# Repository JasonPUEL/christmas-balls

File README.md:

# Christmas Balls

Realization of Christmas ball in PCB, for the pleasure of young and old.
The principle is to build a colored printed circuit.
Programmable colored LEDs will be implemented in a design directly referring to the Christmas spirit.

## General idea

The Christmas balls will have to be autonomous to last the time of the end of year celebrations.
It must be on battery or on pilsner with a small, energy-efficient microcontroller.

A Christmas design should be simple and easily recognizable. It will integrate LEDs cost effectively.

## Shematic

## Board

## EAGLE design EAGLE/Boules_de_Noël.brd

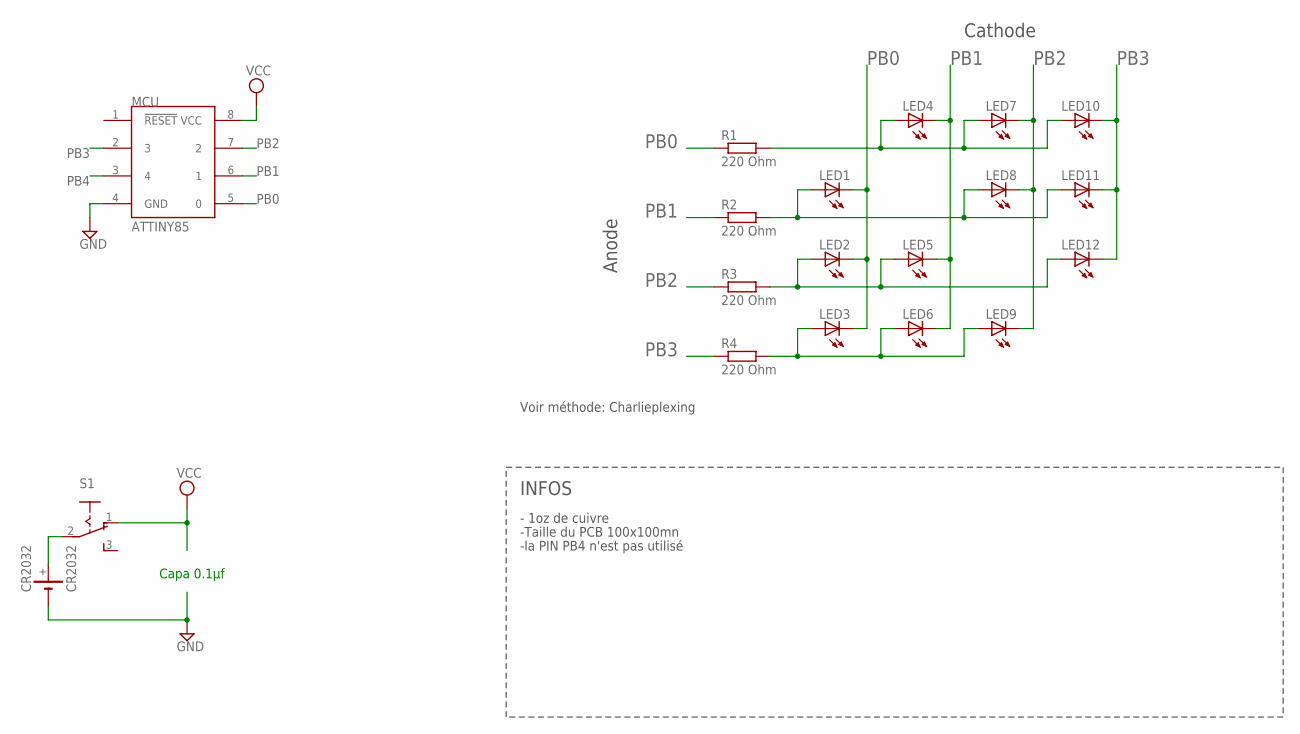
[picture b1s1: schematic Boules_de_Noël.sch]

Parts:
CR2032: CR2032; FRONTCR2032
LED1, LED2, LED3, LED4, LED5, LED6, LED7, LED8, LED9, LED10, LED11, LED12: LEDCHIP-LED0805; CHIP-LED0805
MCU: ATTINY85; 8P3
R1, R2, R3, R4: 220 Ohm; M0805
S1: 255SB

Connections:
GND: CR2032.-, MCU.4 (GND)
unnamed: CR2032.+, S1.2
PB0: LED1.C, LED2.C, LED3.C, MCU.5 (0), R1.1
PB1: LED4.C, LED5.C, LED6.C, MCU.6 (1), R2.1
PB2: LED7.C, LED8.C, LED9.C, MCU.7 (2), R3.1
PB3: LED10.C, LED11.C, LED12.C, MCU.2 (3), R4.1
PB4: MCU.3 (4)
R1: LED4.A, LED7.A, LED10.A, R1.2
R2: LED1.A, LED8.A, LED11.A, R2.2
R3: LED2.A, LED5.A, LED12.A, R3.2
R4: LED3.A, LED6.A, LED9.A, R4.2
VCC: MCU.8 (VCC), S1.1 (O)

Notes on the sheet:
INFOS
Anode
Cathode
- 1oz de cuivre
-Taille du PCB 100x100mn
-la PIN PB4 n'est pas utilisé
Voir méthode: Charlieplexing
Capa 0.1µf

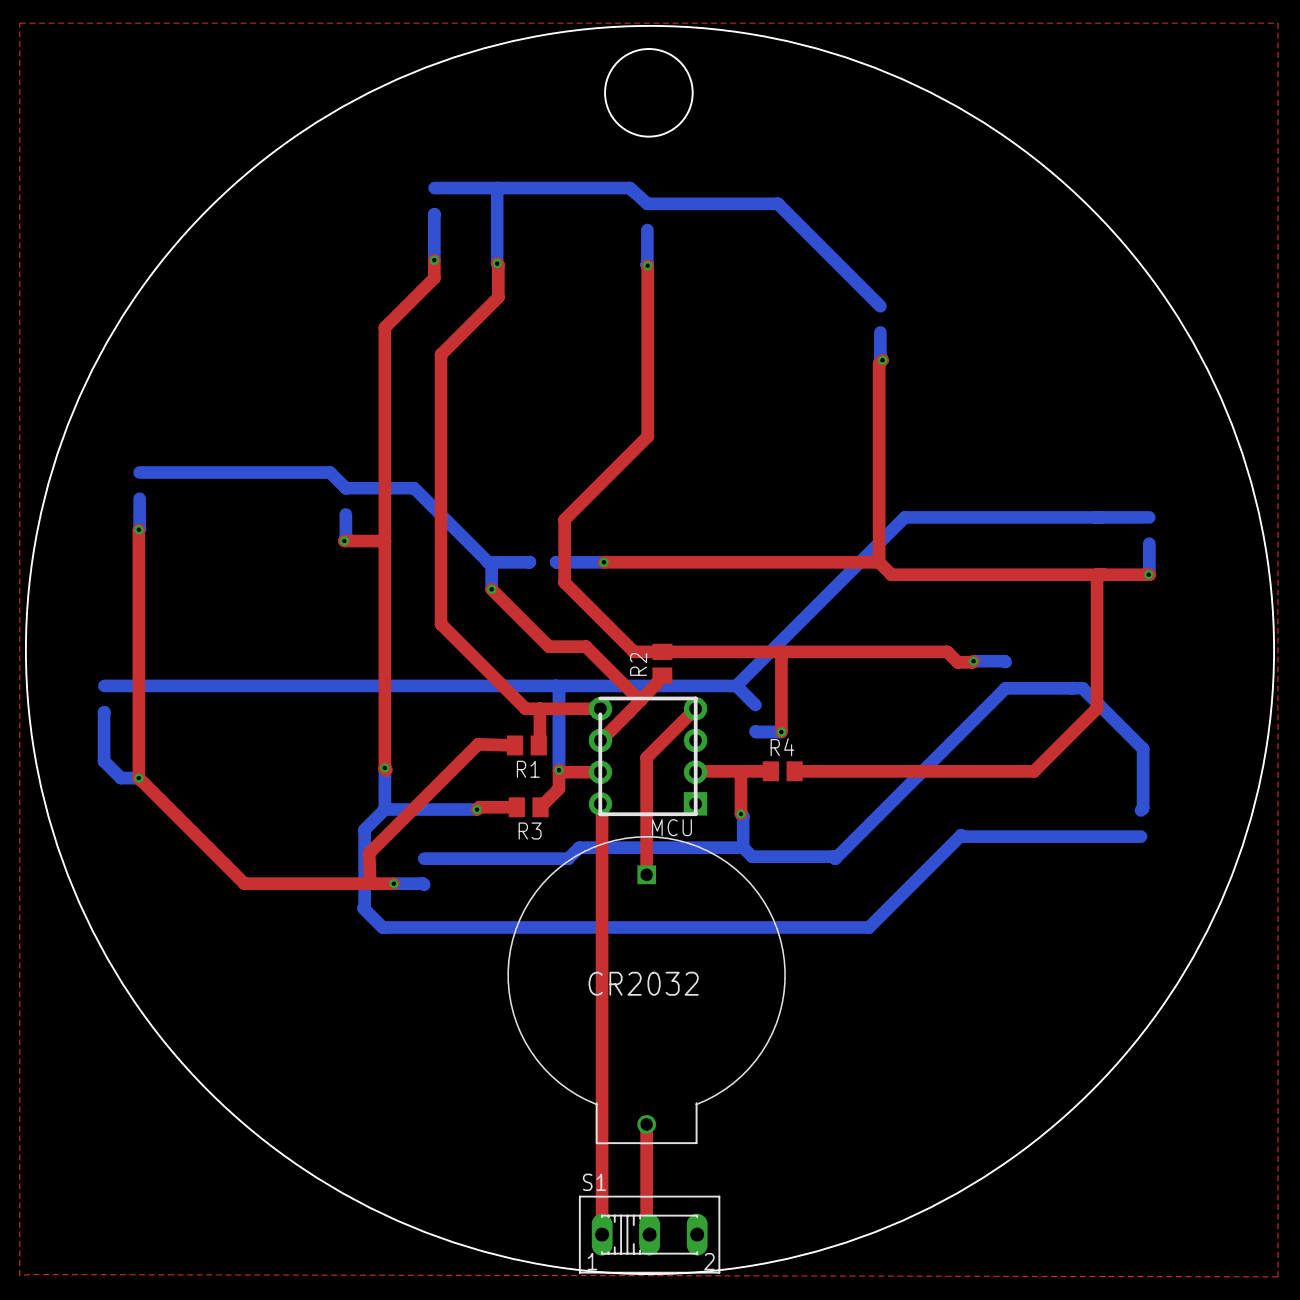
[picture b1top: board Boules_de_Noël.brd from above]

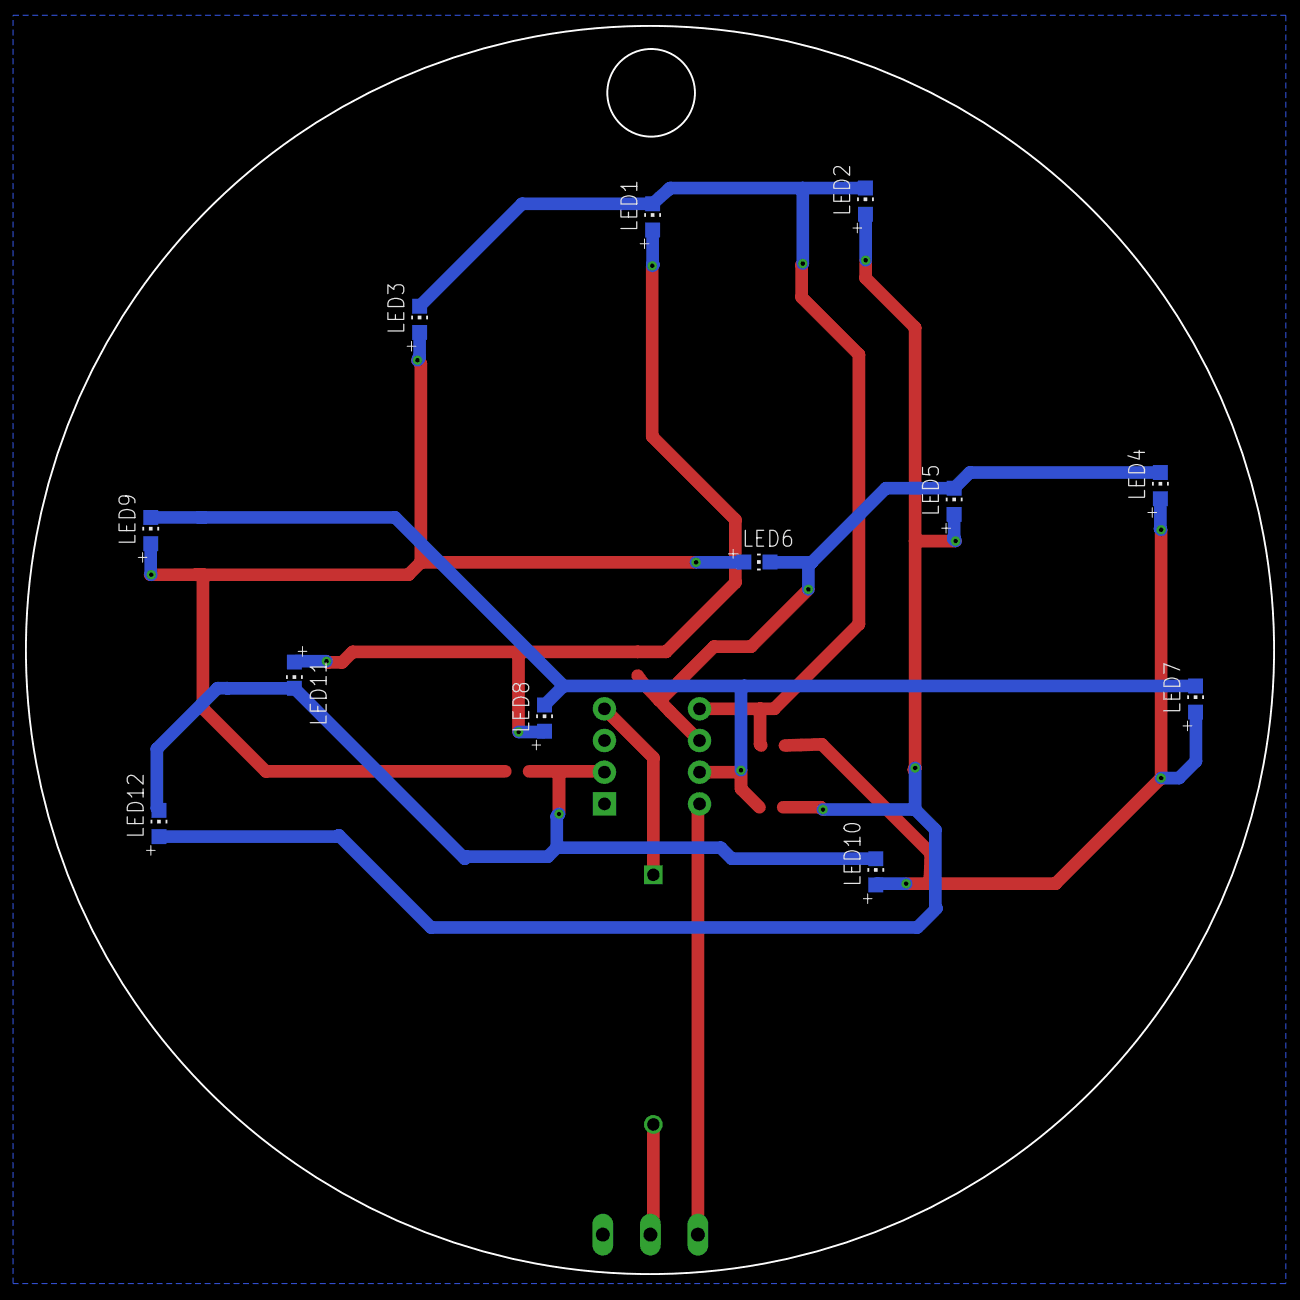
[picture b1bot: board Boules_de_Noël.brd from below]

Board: 2 copper layers, 100.0 x 100.0 mm, 19 parts (12 on the bottom side), 11 nets.

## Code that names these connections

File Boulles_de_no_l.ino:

#define T 500
// a vérifier
#define PB0 2
#define PB1 3
#define PB2 4
#define PB3 5
#define PB4 6

void ledcontrole(bool P0,bool P1,bool P2,bool P3){
    digitalWrite(PB0,P0);
    digitalWrite(PB1,P1);
    digitalWrite(PB2,P2);
    digitalWrite(PB3,P3);
}
void setup() {
  pinMode(PB0,OUTPUT);
  pinMode(PB1,OUTPUT);
  pinMode(PB2,OUTPUT);
  pinMode(PB3,OUTPUT);
  pinMode(PB4,OUTPUT);

ledcontrole(LOW,LOW,LOW,LOW);

}

void loop() {
    ledcontrole(HIGH,LOW,HIGH,LOW);
    delay(T);
    ledcontrole(LOW,HIGH,LOW,HIGH);
    delay(T);
}

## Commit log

2021-03-22 Add Main File
2021-04-27 Add Gitignore
